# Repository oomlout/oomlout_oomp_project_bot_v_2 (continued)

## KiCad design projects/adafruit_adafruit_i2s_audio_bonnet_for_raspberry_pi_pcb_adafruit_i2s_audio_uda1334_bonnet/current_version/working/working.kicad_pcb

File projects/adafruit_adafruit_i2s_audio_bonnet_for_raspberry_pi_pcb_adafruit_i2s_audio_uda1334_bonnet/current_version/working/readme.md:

# adafruit_i2s_audio_bonnet_for_raspberry_pi_pcb
 
## summary 
* id: adafruit_adafruit_i2s_audio_bonnet_for_raspberry_pi_pcb_adafruit_i2s_audio_uda1334_bonnet
* user: adafruit
* name: adafruit_i2s_audio_bonnet_for_raspberry_pi_pcb
* board: adafruit_i2s_audio_uda1334_bonnet
* repo: https://github.com/adafruit/Adafruit-I2S-Audio-Bonnet-for-Raspberry-Pi-PCB

* src_file_repo_sch: 
* src_file_repo_sch_link: https://github.com/adafruit/Adafruit-I2S-Audio-Bonnet-for-Raspberry-Pi-PCB/tree/master/
* full details link: https://github.com/oomlout/oomlout_oomp_project_bot_v_2/tree/main/projects/adafruit_adafruit_i2s_audio_bonnet_for_raspberry_pi_pcb_adafruit_i2s_audio_uda1334_bonnet/current_version/working  

## schematic  
  
[schematic (pdf)](working_schematic.pdf) 

## pcb  

[board (pdf)](working.pdf)  

## working_bom
| Id | Designator | Footprint | Quantity | Designation | Supplier and ref |  | None | 
| --- | --- | --- | --- | --- | --- | --- | --- | 
| 1 | FID2,FID1 | FIDUCIAL_1MM | 2 | FIDUCIAL_1MM |  |  | [''] | 
| 2 | R2,R1 | 0603-NO | 2 | 10K |  |  | [''] | 
| 3 | U1 | SSOP16_4.4MM | 1 | UDA1334ATS |  |  | [''] | 
| 4 | U$11 | PCBFEAT-REV-040 | 1 |  |  |  | [''] | 
| 5 | C1,C2,C3 | 0603-NO | 3 | 0.1uF |  |  | [''] | 
| 6 | R5,R3 | 0603-NO | 2 | 220k |  |  | [''] | 
| 7 | JP6,JP5,JP1,JP3 | 1X02_ROUND | 4 |  |  |  | [''] | 
| 8 | C8,C7 | 0603-NO | 2 | 0.01uF |  |  | [''] | 
| 9 | U2 | SOT23-5 | 1 | AP2112-3.3K |  |  | [''] | 
| 10 | FB1,FB2 | 0805 | 2 | Ferrite |  |  | [''] | 
| 11 | CONN2 | RCA_DUAL_JACK | 1 | AUDIO_DUAL_RCA |  |  | [''] | 
| 12 | U$5 | ADAFRUIT_5MM | 1 |  |  |  | [''] | 
| 13 | C13,C11,C14,C5 | 0805-NO | 4 | 10uF |  |  | [''] | 
| 14 | C4,C6 | PANASONIC_C | 2 | 47uF |  |  | [''] | 
| 15 | R4,R6 | 0603-NO | 2 | 100 |  |  | [''] | 
| 16 | JP4 | 1X23_ROUND_70MIL | 1 |  |  |  | [''] | 
| 17 | Q1 | SOT23-WIDE | 1 |  DMG2305 |  |  | [''] | 
| 18 | X2 | 4UCONN_19269 | 1 | 19269 |  |  | [''] | 
| 19 | RPI1 | PI_BONNET_THMSMT | 1 | RASPBERRYPI_BPLUS_BONNET_THMSMT |  |  | [''] | 
| 20 | SJ2 | SOLDERJUMPER_CLOSEDWIRE | 1 |  |  |  | [''] | 

## bom_schematic
| Ref | Qnty | Value | Cmp name | Footprint | Description | Vendor | DNP | 
| --- | --- | --- | --- | --- | --- | --- | --- | 
| C1, C2, C3 | 3 | 0.1uF | CAP_CERAMIC0603_NO | working:0603-NO |  |  |  | 
| C4, C6 | 2 | 47uF | CAP_ELECTROLYTICPANASONIC_C | working:PANASONIC_C |  |  |  | 
| C5, C11, C13, C14 | 4 | 10uF | CAP_CERAMIC0805-NOOUTLINE | working:0805-NO |  |  |  | 
| C7, C8 | 2 | 0.01uF | CAP_CERAMIC0603_NO | working:0603-NO |  |  |  | 
| CONN2 | 1 | AUDIO_DUAL_RCA | AUDIO_DUAL_RCA | working:RCA_DUAL_JACK |  |  |  | 
| FB1, FB2 | 2 | Ferrite | FERRITE0805 | working:0805 |  |  |  | 
| FID1, FID2 | 2 | FIDUCIAL_1MM | FIDUCIAL_1MM | working:FIDUCIAL_1MM |  |  |  | 
| JP1, JP3, JP5, JP6 | 4 | HEADER-1X2ROUND | HEADER-1X2ROUND | working:1X02_ROUND |  |  |  | 
| JP4 | 1 | HEADER-1X23 | HEADER-1X23 | working:1X23_ROUND_70MIL |  |  |  | 
| Q1 | 1 |  DMG2305 | MOSFET-PWIDE | working:SOT23-WIDE |  |  |  | 
| R1, R2 | 2 | 10K | RESISTOR_0603_NOOUT | working:0603-NO |  |  |  | 
| R3, R5 | 2 | 220k | RESISTOR_0603_NOOUT | working:0603-NO |  |  |  | 
| R4, R6 | 2 | 100 | RESISTOR_0603_NOOUT | working:0603-NO |  |  |  | 
| RPI1 | 1 | RASPBERRYPI_BPLUS_BONNET_THMSMT | RASPBERRYPI_BPLUS_BONNET_THMSMT | working:PI_BONNET_THMSMT |  |  |  | 
| SJ2 | 1 | SOLDERJUMPER_CLOSED | SOLDERJUMPER_CLOSED | working:SOLDERJUMPER_CLOSEDWIRE |  |  |  | 
| U1 | 1 | UDA1334ATS | AUDIO_I2S_UDA1334{dblquote}{dblquote} | working:SSOP16_4.4MM |  |  |  | 
| U2 | 1 | AP2112-3.3K | VREG_SOT23-5 | working:SOT23-5 |  |  |  | 
| X2 | 1 | 19269 | AUDIO_3.5MMJACK | working:4UCONN_19269 |  |  |  |

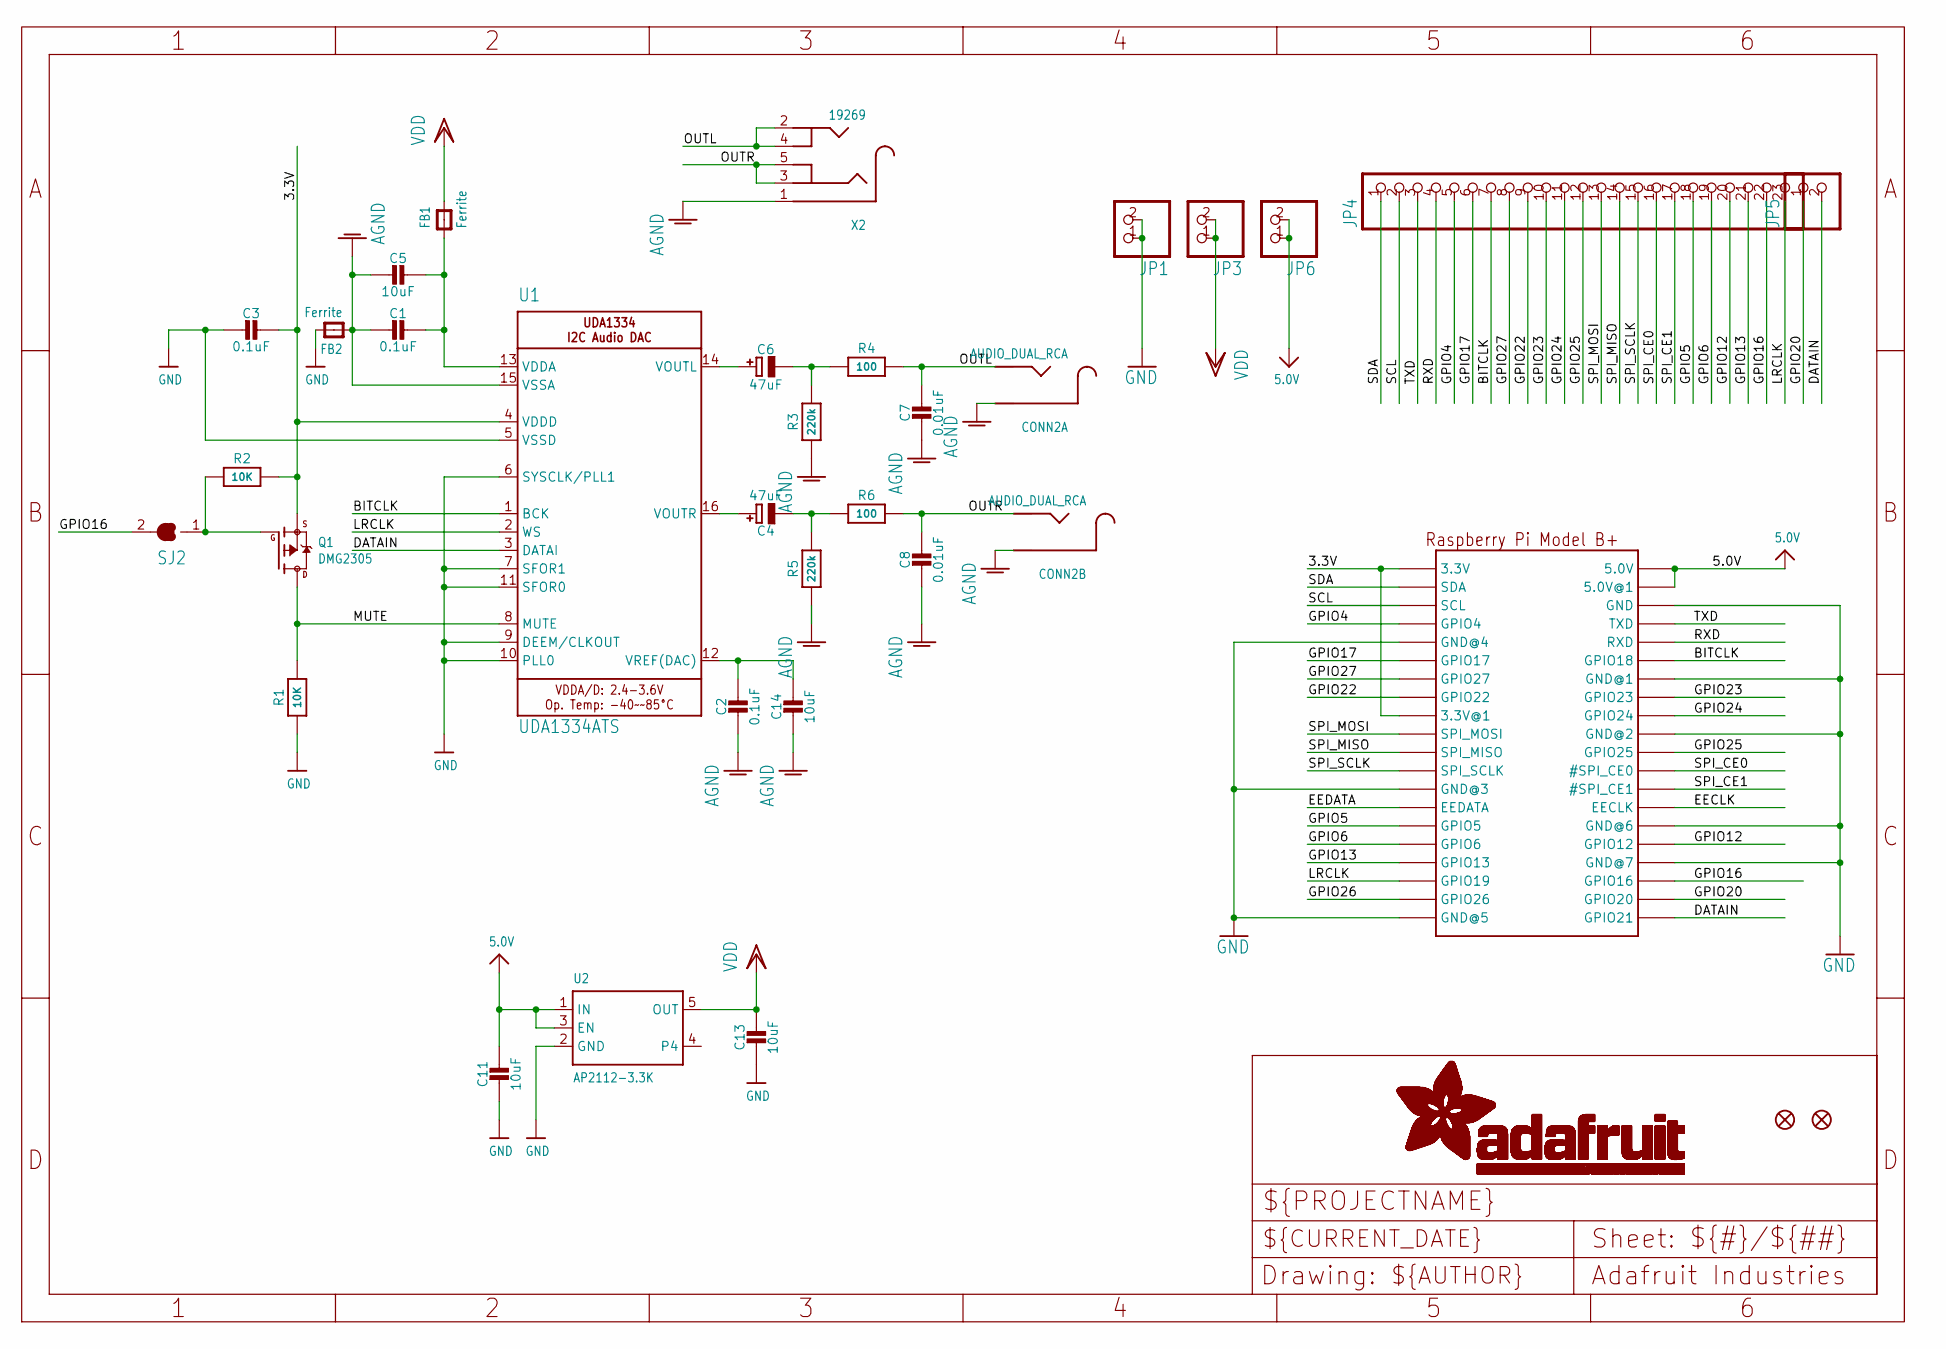
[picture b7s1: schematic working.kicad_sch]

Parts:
C1, C2, C3: 0.1uF; 0603-NO
C4, C6: 47uF; PANASONIC_C
C5, C11, C13, C14: 10uF; 0805-NO
C7, C8: 0.01uF; 0603-NO
CONN2: AUDIO_DUAL_RCA; RCA_DUAL_JACK
FB1, FB2: Ferrite; 0805
FID1, FID2: FIDUCIAL_1MM
JP1, JP3, JP5, JP6: HEADER-1X2ROUND; 1X02_ROUND
JP4: HEADER-1X23; 1X23_ROUND_70MIL
Q1: DMG2305; SOT23-WIDE
R1, R2: 10K; 0603-NO
R3, R5: 220k; 0603-NO
R4, R6: 100; 0603-NO
RPI1: RASPBERRYPI_BPLUS_BONNET_THMSMT; PI_BONNET_THMSMT
SJ2: SOLDERJUMPER_CLOSED; SOLDERJUMPER_CLOSEDWIRE
U1: UDA1334ATS; SSOP16_4.4MM
U2: AP2112-3.3K; SOT23-5
X2: 19269; 4UCONN_19269

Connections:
3.3V: C3.1, Q1.2 (S), R2.2, RPI1.1 (3.3V), RPI1.17 (3.3V@1), RPI1.S1 (3.3V), RPI1.S17 (3.3V@1), U1.4 (VDDD)
5.0V: C11.1, JP6.1, JP6.2, RPI1.2 (5.0V), RPI1.4 (5.0V@1), RPI1.S2 (5.0V), RPI1.S4 (5.0V@1), U2.1 (IN), U2.3 (EN)
AGND: C1.2, C2.2, C5.2, C7.2, C8.2, C14.2, CONN2.L_G (SLEEVE), CONN2.L_G' (SLEEVE), CONN2.R_G (SLEEVE), CONN2.R_G' (SLEEVE), FB2.1, R3.1, R5.1, U1.15 (VSSA), X2.1
BITCLK: JP4.7, RPI1.12 (GPIO18), RPI1.S12 (GPIO18), U1.1 (BCK)
DATAIN: JP5.2, RPI1.40 (GPIO21), RPI1.S40 (GPIO21), U1.3 (DATAI)
EECLK: RPI1.28 (EECLK), RPI1.S28 (EECLK)
EEDATA: RPI1.27 (EEDATA), RPI1.S27 (EEDATA)
GND: C3.2, C11.2, C13.2, FB2.2, JP1.1, JP1.2, R1.1, RPI1.6 (GND), RPI1.9 (GND@4), RPI1.14 (GND@1), RPI1.20 (GND@2), RPI1.25 (GND@3), RPI1.30 (GND@6), RPI1.34 (GND@7), RPI1.39 (GND@5), RPI1.S6 (GND), RPI1.S9 (GND@4), RPI1.S14 (GND@1), RPI1.S20 (GND@2), RPI1.S25 (GND@3), RPI1.S30 (GND@6), RPI1.S34 (GND@7), RPI1.S39 (GND@5), U1.5 (VSSD), U1.6 (SYSCLK/PLL1), U1.7 (SFOR1), U1.9 (DEEM/CLKOUT), U1.10 (PLL0), U1.11 (SFOR0), U2.2 (GND)
GPIO4: JP4.5, RPI1.7 (GPIO4), RPI1.S7 (GPIO4)
GPIO5: JP4.18, RPI1.29 (GPIO5), RPI1.S29 (GPIO5)
GPIO6: JP4.19, RPI1.31 (GPIO6), RPI1.S31 (GPIO6)
GPIO12: JP4.20, RPI1.32 (GPIO12), RPI1.S32 (GPIO12)
GPIO13: JP4.21, RPI1.33 (GPIO13), RPI1.S33 (GPIO13)
GPIO16: JP4.22, RPI1.36 (GPIO16), RPI1.S36 (GPIO16), SJ2.2
GPIO17: JP4.6, RPI1.11 (GPIO17), RPI1.S11 (GPIO17)
GPIO20: JP5.1, RPI1.38 (GPIO20), RPI1.S38 (GPIO20)
GPIO22: JP4.9, RPI1.15 (GPIO22), RPI1.S15 (GPIO22)
GPIO23: JP4.10, RPI1.16 (GPIO23), RPI1.S16 (GPIO23)
GPIO24: JP4.11, RPI1.18 (GPIO24), RPI1.S18 (GPIO24)
GPIO25: JP4.12, RPI1.22 (GPIO25), RPI1.S22 (GPIO25)
GPIO26: RPI1.37 (GPIO26), RPI1.S37 (GPIO26)
GPIO27: JP4.8, RPI1.13 (GPIO27), RPI1.S13 (GPIO27)
LRCLK: JP4.23, RPI1.35 (GPIO19), RPI1.S35 (GPIO19), U1.2 (WS)
MUTE: Q1.3 (D), R1.2, U1.8 (MUTE)
unnamed: C2.1, C14.1, U1.12 (VREF(DAC))
unnamed: C1.1, C5.1, FB1.1, U1.13 (VDDA)
unnamed: C4.+, U1.16 (VOUTR)
unnamed: Q1.1 (G), R2.1, SJ2.1
unnamed: C6.+, U1.14 (VOUTL)
unnamed: C6.-, R3.2, R4.1
unnamed: C4.-, R5.2, R6.1
OUTL: C7.1, CONN2.L_SIG (TIP), CONN2.L_SIG' (TIP), R4.2, X2.2, X2.4
OUTR: C8.1, CONN2.R_SIG (TIP), CONN2.R_SIG' (TIP), R6.2, X2.3, X2.5
RXD: JP4.4, RPI1.10 (RXD), RPI1.S10 (RXD)
SCL: JP4.2, RPI1.5 (SCL), RPI1.S5 (SCL)
SDA: JP4.1, RPI1.3 (SDA), RPI1.S3 (SDA)
SPI_CE0: JP4.16, RPI1.24 (#SPI_CE0), RPI1.S24 (#SPI_CE0)
SPI_CE1: JP4.17, RPI1.26 (#SPI_CE1), RPI1.S26 (#SPI_CE1)
SPI_MISO: JP4.14, RPI1.21 (SPI_MISO), RPI1.S21 (SPI_MISO)
SPI_MOSI: JP4.13, RPI1.19 (SPI_MOSI), RPI1.S19 (SPI_MOSI)
SPI_SCLK: JP4.15, RPI1.23 (SPI_SCLK), RPI1.S23 (SPI_SCLK)
TXD: JP4.3, RPI1.8 (TXD), RPI1.S8 (TXD)
VDD: C13.1, FB1.2, JP3.1, JP3.2, U2.5 (OUT)

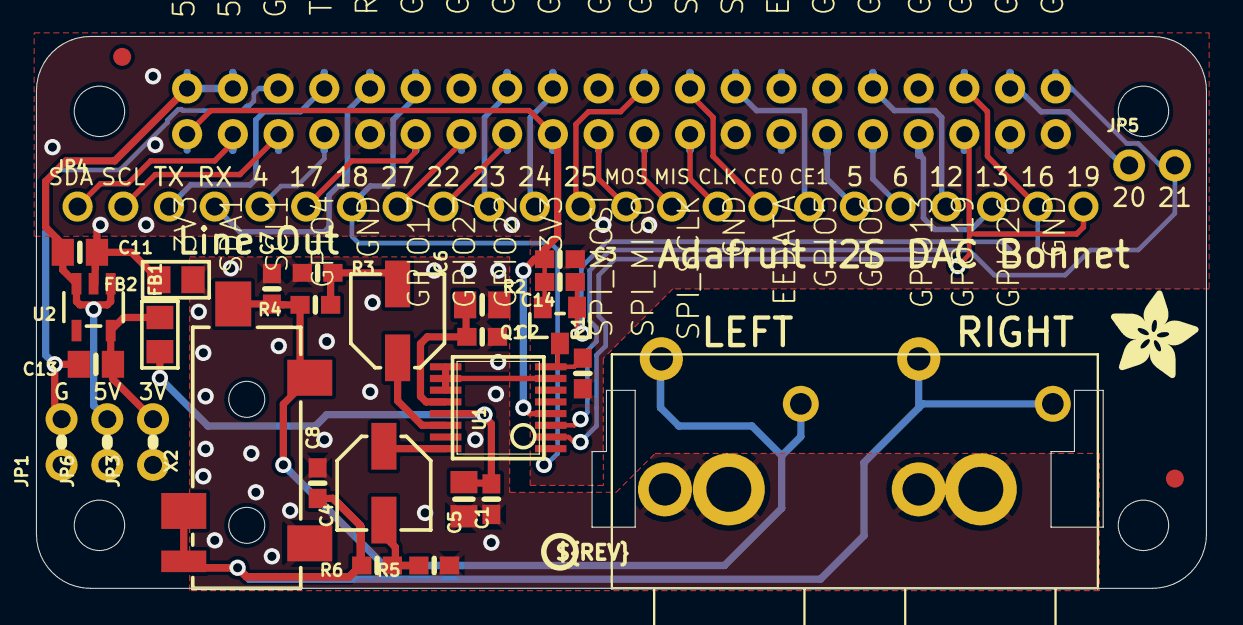
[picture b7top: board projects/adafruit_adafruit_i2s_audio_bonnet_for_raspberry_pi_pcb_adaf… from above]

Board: 2 copper layers, 65.0 x 30.7 mm, 35 parts (1 on the bottom side), 43 nets.

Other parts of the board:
U$5: ADAFRUIT_5MM
U$11: PCBFEAT-REV-040
